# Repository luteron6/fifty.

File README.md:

# fifty.

This is my take on a minimalist 50% keyboard optimized for commandlines. I created it to solve a problem controlling the computer in my travel van. There's a monitor and computer mounted in the vehicle, but when I'm using it, there's no good spot to put the keyboard. It could go on my lap, but it's huge (~90% keyboard). And there's no spot for a mouse or touchpad. This solves both these problems. At first the goal was to create a 40% keyboard with a touchpad, but it ended up being a 50% keyboard (48 keys) with a round touchpad and right/left mouse buttons. It uses MX Brown switches, a Cirque trackpad, all powered by a Waveshare RP2040-Plus:
<br><br>

It's made to run this keymap:
<br><br>

## CAD
The case is stored in the /CAD folder, both the STL files and the STEP file. Meant to be 3D printed. Everything bolts together with M2 screws and threaded inserts. Also has rubber feet on the bottom.

## PCB
The PCB gerbers and source files are stored in the /PCB folder. I made it in KiCAD:

It needs:
* MX-Style Switches (50)
* SOD-123 Diodes (50)
* Cirque 40mm Trackpad
* 4.7k ohm Resistors (2)
* RP2040-Plus
* Screw-In Stabilizers (1x 2u and 1x 6.25u)

## Code
I made the code in QMK. Source files are in the /Code folder. Still a work in progress, but QMK MSYS can build it, so I put the .uf2 file in the folder. I might still change the layout, but currently it's documented above.

## BOM
| Item                      | QTY Needed | QTY Purchased | Price   | Description                | Link                                                                                                                  |
|---------------------------|------------|---------------|---------|----------------------------|-----------------------------------------------------------------------------------------------------------------------|
| MX Brown Switches         | 50         | 70            | $24.99  | Keyboard Switches!         | [link](https://www.amazon.com/Pre-lubed-Switches-Mechanical-Keyboard-Pcs-5pin/dp/B0CKTJLCDB)                                  |
| Cirque Trackpad           | 1          | 1             | $27.00  | Trackpad Module            | [link](https://shop.beekeeb.com/product/40mm-cirque-glidepoint-circle-trackpad-module-diy-kit-for-split-mechanical-keyboard/) |
| RP2040-Plus               | 1          | 1             | $6.99   | Microcontroller            | [link](https://www.waveshare.com/rp2040-plus.htm?sku=23503)                                                                   |
| USB-C Connector           | 1          | 1             | $12.99  | USB-C adapter              | [link](https://www.amazon.com/Tciogrxp-Magnetic-Connector-Compatible-Thunderbolt/dp/B0DFM1B3DK/)                              |
| Stabilizers               | 1          | 1             | $16.98  | Screw-In Stabilizers       | [link](https://www.amazon.com/DUROCK-Stabilizers-Translucent-Keyboard-Mechanical/dp/B0B2RVN19F/)                              |
| Diodes                    | 50         | 100           | $6.99   | SOD-123 1N4148W SMD Diodes | [link](https://www.amazon.com/100-Pieces-1N4148W-Switching-High-Speed/dp/B079KJX5J9/)                                         |
| Rubber Feet               | 4          | 12            | $5.99   | Rubber Silicone Feet       | [link](https://www.amazon.com/Pack-Rubber-Silicone-Feet-Diameter/dp/B0927HC2TD/)                                              |
| Keycaps                   | 1          | 1             | $14.69  | Low Profile Keycaps!       | [link](https://www.amazon.com/XVX-Profile-Keycaps-Keyboard-Mechanical/dp/B0C1B6STX4)                                          |
| Resistors                 | 2          | 3250          | $7.99   | SMD resistors              | [link](https://www.amazon.com/Yobett-3250PCS-Resistor-Tolerance-Resistors/dp/B0BZGQ8136/)                                     |
| PCB (ordered from JLCPCB) | 1          | 5             | $15.00  |                            |                                                                                                                       |
| Sales Tax                 |            |               | $10.82  |                            |                                                                                                                       |
| Shipping                  |            |               | $30.00  | JLCPCB Shipping            |                                                                                                                       |
| Shipping                  |            |               | $15.00  | beekeeb Shipping           |                                                                                                                       |
|                           |            |               |         |                            |                                                                                                                       |
| TOTAL                     |            |               | $195.43 |                            |                                                                                                                       |

made with love by a hack clubber

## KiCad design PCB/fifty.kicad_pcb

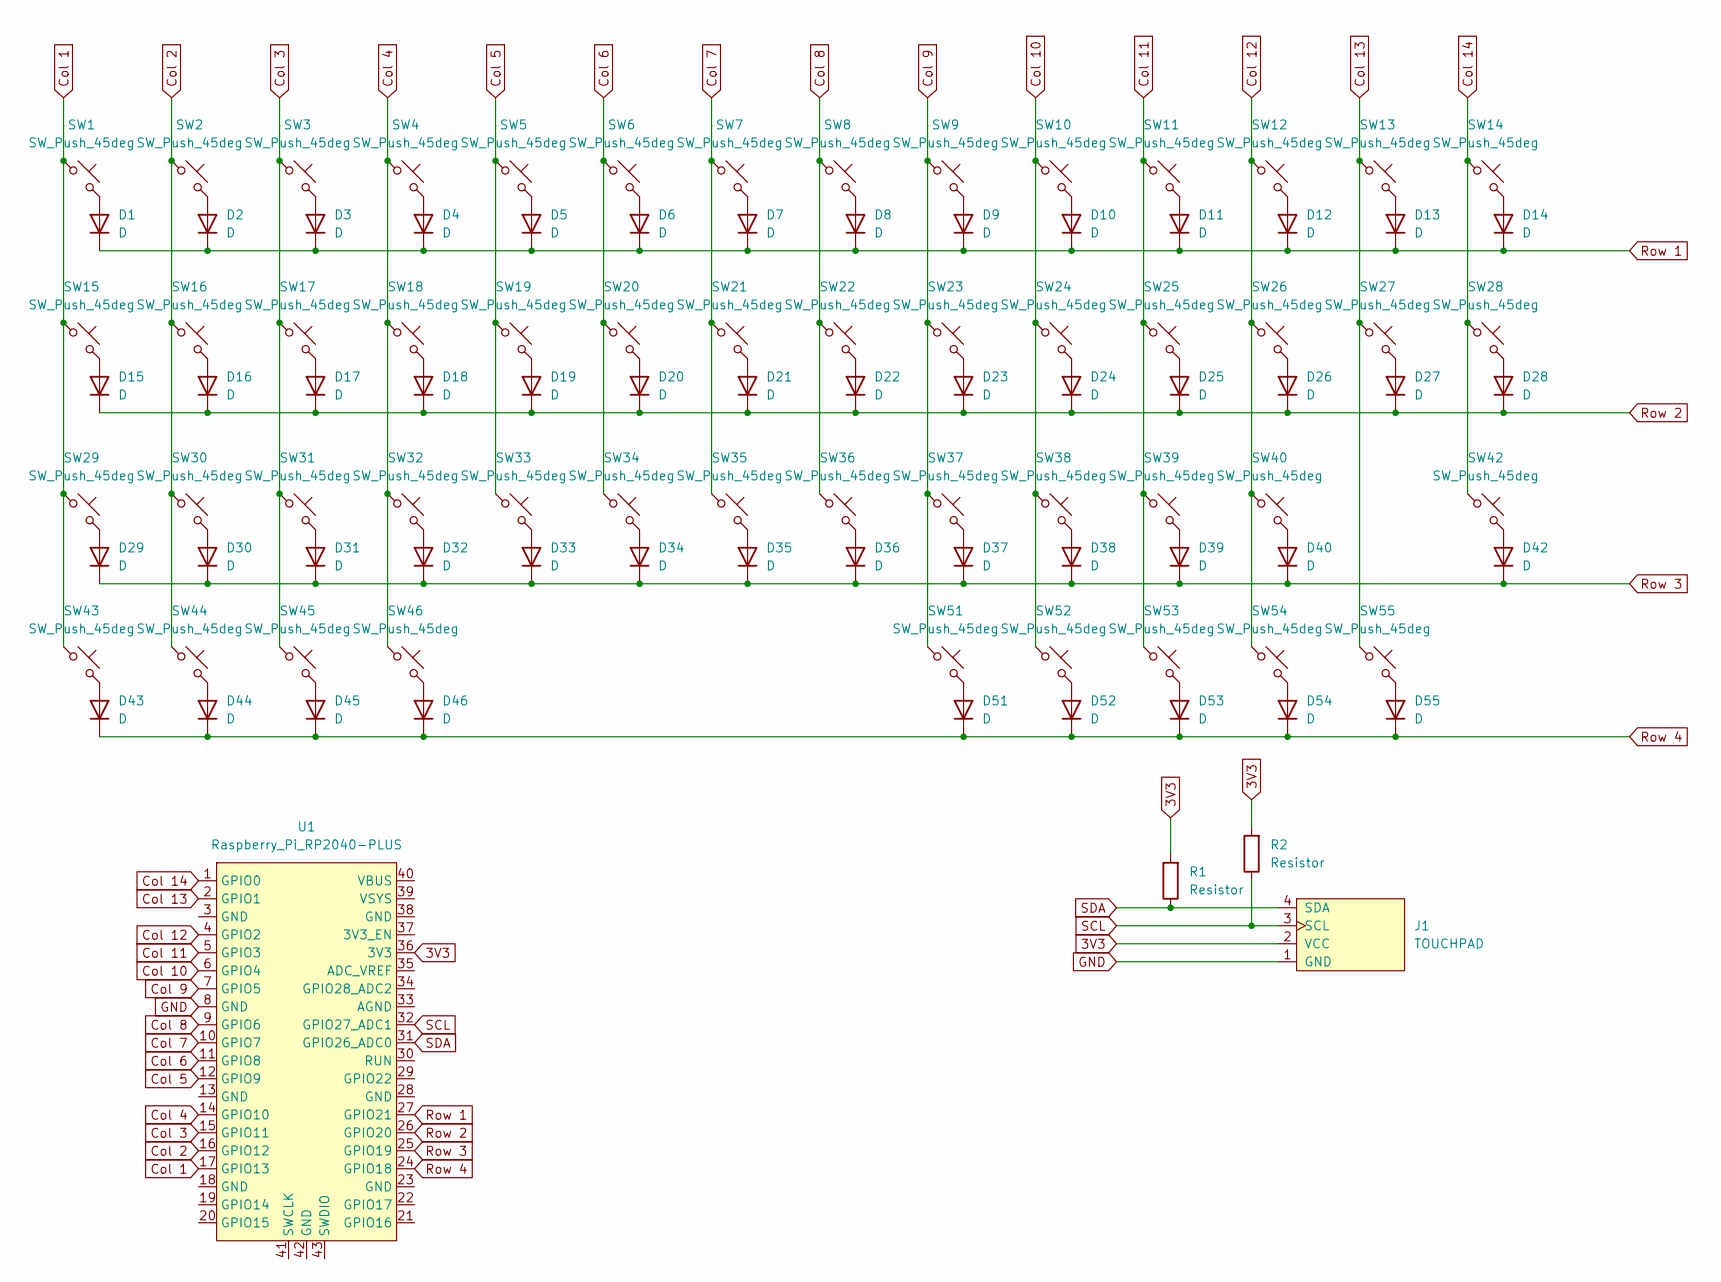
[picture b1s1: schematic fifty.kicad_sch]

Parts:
D1, D2, D3, D4, D5, D6, D7, D8, D9, D10, D11, D12, D13, D14, D15, D16, D17, D18, D19, D20, D21, D22, D23, D24, D25, D26, D27, D28, D29, D30, D31, D32, D33, D34, D35, D36, D37, D38, D39, D40, D42, D43, D44, D45, D46, D51, D52, D53, D54, D55: D; D_SOD-123
J1: TOUCHPAD; Touchpad
R1, R2: Resistor; R_0402_1005Metric
SW1, SW43, SW44, SW51: SW_Push_45deg; MX_PCB_1.25u
SW2, SW3, SW4, SW5, SW6, SW7, SW8, SW9, SW10, SW11, SW12, SW13, SW14, SW16, SW17, SW18, SW19, SW20, SW21, SW22, SW23, SW24, SW25, SW26, SW28, SW30, SW31, SW32, SW33, SW34, SW35, SW36, SW37, SW38, SW39, SW42, SW45, SW52, SW53, SW54, SW55: SW_Push_45deg; MX_PCB_1.00u
SW15: SW_Push_45deg; MX_PCB_1.50u
SW27, SW40: SW_Push_45deg; MX_PCB_1.75u
SW29: SW_Push_45deg; MX_PCB_2.00u
SW46: SW_Push_45deg; MX_PCB_6.25u
U1: Raspberry_Pi_RP2040-PLUS; Raspberry_Pi_Pico

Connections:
3V3: J1.2 (VCC), R1.2, R2.2, U1.36 (3V3)
Col 1: SW1.1, SW15.1, SW29.1, SW43.1, U1.17 (GPIO13)
Col 2: SW2.1, SW16.1, SW30.1, SW44.1, U1.16 (GPIO12)
Col 3: SW3.1, SW17.1, SW31.1, SW45.1, U1.15 (GPIO11)
Col 4: SW4.1, SW18.1, SW32.1, SW46.1, U1.14 (GPIO10)
Col 5: SW5.1, SW19.1, SW33.1, U1.12 (GPIO9)
Col 6: SW6.1, SW20.1, SW34.1, U1.11 (GPIO8)
Col 7: SW7.1, SW21.1, SW35.1, U1.10 (GPIO7)
Col 8: SW8.1, SW22.1, SW36.1, U1.9 (GPIO6)
Col 9: SW9.1, SW23.1, SW37.1, SW51.1, U1.7 (GPIO5)
Col 10: SW10.1, SW24.1, SW38.1, SW52.1, U1.6 (GPIO4)
Col 11: SW11.1, SW25.1, SW39.1, SW53.1, U1.5 (GPIO3)
Col 12: SW12.1, SW26.1, SW40.1, SW54.1, U1.4 (GPIO2)
Col 13: SW13.1, SW27.1, SW55.1, U1.2 (GPIO1)
Col 14: SW14.1, SW28.1, SW42.1, U1.1 (GPIO0)
GND: J1.1 (GND), U1.8 (GND)
unnamed: D1.2 (A), SW1.2
unnamed: D2.2 (A), SW2.2
unnamed: D3.2 (A), SW3.2
unnamed: D4.2 (A), SW4.2
unnamed: D5.2 (A), SW5.2
unnamed: D6.2 (A), SW6.2
unnamed: D7.2 (A), SW7.2
unnamed: D8.2 (A), SW8.2
unnamed: D9.2 (A), SW9.2
unnamed: D10.2 (A), SW10.2
unnamed: D11.2 (A), SW11.2
unnamed: D12.2 (A), SW12.2
unnamed: D13.2 (A), SW13.2
unnamed: D14.2 (A), SW14.2
unnamed: D15.2 (A), SW15.2
unnamed: D16.2 (A), SW16.2
unnamed: D17.2 (A), SW17.2
unnamed: D18.2 (A), SW18.2
unnamed: D19.2 (A), SW19.2
unnamed: D20.2 (A), SW20.2
unnamed: D21.2 (A), SW21.2
unnamed: D22.2 (A), SW22.2
unnamed: D23.2 (A), SW23.2
unnamed: D24.2 (A), SW24.2
unnamed: D25.2 (A), SW25.2
unnamed: D26.2 (A), SW26.2
unnamed: D27.2 (A), SW27.2
unnamed: D28.2 (A), SW28.2
unnamed: D29.2 (A), SW29.2
unnamed: D30.2 (A), SW30.2
unnamed: D31.2 (A), SW31.2
unnamed: D32.2 (A), SW32.2
unnamed: D33.2 (A), SW33.2
unnamed: D34.2 (A), SW34.2
unnamed: D35.2 (A), SW35.2
unnamed: D36.2 (A), SW36.2
unnamed: D37.2 (A), SW37.2
unnamed: D38.2 (A), SW38.2
unnamed: D39.2 (A), SW39.2
unnamed: D40.2 (A), SW40.2
unnamed: D42.2 (A), SW42.2
unnamed: D43.2 (A), SW43.2
unnamed: D44.2 (A), SW44.2
unnamed: D45.2 (A), SW45.2
unnamed: D46.2 (A), SW46.2
unnamed: D51.2 (A), SW51.2
unnamed: D52.2 (A), SW52.2
unnamed: D53.2 (A), SW53.2
unnamed: D54.2 (A), SW54.2
unnamed: D55.2 (A), SW55.2
Row 1: D1.1 (K), D2.1 (K), D3.1 (K), D4.1 (K), D5.1 (K), D6.1 (K), D7.1 (K), D8.1 (K), D9.1 (K), D10.1 (K), D11.1 (K), D12.1 (K), D13.1 (K), D14.1 (K), U1.27 (GPIO21)
Row 2: D15.1 (K), D16.1 (K), D17.1 (K), D18.1 (K), D19.1 (K), D20.1 (K), D21.1 (K), D22.1 (K), D23.1 (K), D24.1 (K), D25.1 (K), D26.1 (K), D27.1 (K), D28.1 (K), U1.26 (GPIO20)
Row 3: D29.1 (K), D30.1 (K), D31.1 (K), D32.1 (K), D33.1 (K), D34.1 (K), D35.1 (K), D36.1 (K), D37.1 (K), D38.1 (K), D39.1 (K), D40.1 (K), D42.1 (K), U1.25 (GPIO19)
Row 4: D43.1 (K), D44.1 (K), D45.1 (K), D46.1 (K), D51.1 (K), D52.1 (K), D53.1 (K), D54.1 (K), D55.1 (K), U1.24 (GPIO18)
SCL: J1.3 (SCL), R2.1, U1.32 (GPIO27_ADC1)
SDA: J1.4 (SDA), R1.1, U1.31 (GPIO26_ADC0)

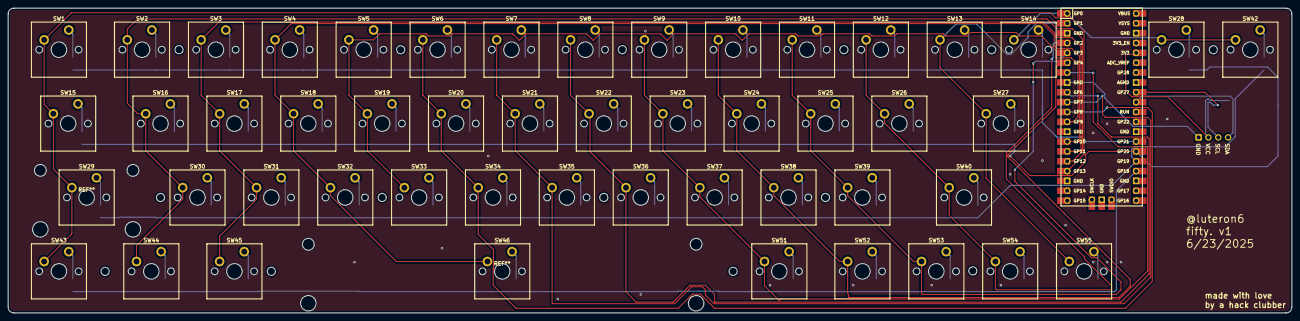
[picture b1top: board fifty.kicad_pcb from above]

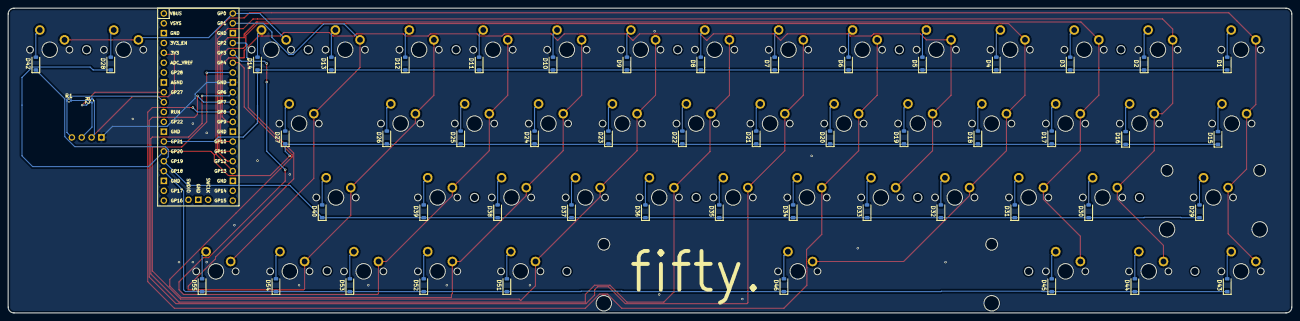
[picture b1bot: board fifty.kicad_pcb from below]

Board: 2 copper layers, 331.0 x 78.6 mm, 104 parts (52 on the bottom side), 72 nets.

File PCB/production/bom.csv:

Designator,Footprint,Quantity,Value,LCSC Part #
"D1, D10, D11, D12, D13, D14, D15, D16, D17, D18, D19, D2, D20, D21, D22, D23, D24, D25, D26, D27, D28, D29, D3, D30, D31, D32, D33, D34, D35, D36, D37, D38, D39, D4, D40, D42, D43, D44, D45, D46, D5, D51, D52, D53, D54, D55, D6, D7, D8, D9",D_SOD-123,50,D,
J1,Touchpad,1,TOUCHPAD,
"R1, R2",0402,2,Resistor,
"SW1, SW43, SW44, SW51",MX_PCB_1.25u,4,SW_Push_45deg,
"SW10, SW11, SW12, SW13, SW14, SW16, SW17, SW18, SW19, SW2, SW20, SW21, SW22, SW23, SW24, SW25, SW26, SW28, SW3, SW30, SW31, SW32, SW33, SW34, SW35, SW36, SW37, SW38, SW39, SW4, SW42, SW45, SW5, SW52, SW53, SW54, SW55, SW6, SW7, SW8, SW9",MX_PCB_1.00u,41,SW_Push_45deg,
SW15,MX_PCB_1.50u,1,SW_Push_45deg,
"SW27, SW40",MX_PCB_1.75u,2,SW_Push_45deg,
SW29,MX_PCB_2.00u,1,SW_Push_45deg,
SW46,MX_PCB_6.25u,1,SW_Push_45deg,
U1,Raspberry_Pi_Pico,1,Raspberry_Pi_RP2040-PLUS,

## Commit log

2025-06-03 Created JOURNAL.md! Logged Day 1
2025-06-05 Day 2!
2025-06-13 Day 3!
2025-06-14 More Day 3
2025-06-15 Day 4!
2025-06-15 Added to BOM
2025-06-16 Changed name to fifty.
2025-06-16 Day 5
2025-06-17 Day 6!
2025-06-17 Added files
2025-06-17 uploaded case STEP file
2025-06-17 Add BOM in CSV format
2025-06-18 shortened links
2025-07-27 Updated all files since building project
